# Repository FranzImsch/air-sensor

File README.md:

# Air Sensor V1.0
A small solar powered ZigBee compatible sensor with energy harvesting for temperature, humidity and VOCs.  
Features nRF52840, AEM10941, SHT40 and SGP40.

## Known Flaws
* Due to the extremely high resistor values of the voltage dividers and their corresponding errors, the set voltage limits are very inaccurate. 
* The overall performance is not completely satisfying, especially indoors pretty much no energy is harvested. (Maybe a different chip like TI's [BQ25570](https://www.ti.com/lit/ds/symlink/bq25570.pdf) could perform better.) The Sensirion sensors perform excellently.

## Software
The proper software (that uses ZigBee) is to be developed. The existing software is a very rudimentary Arduino example to test the sensors. It draws way too much power to be used.

## BOM
The interactive BOM can be found [here](https://franz.science/airsensor-v1.0-ibom/).  

## Reference
e-peas Configuration tool (for the resistors) in the resources section: [Product page](https://e-peas.com/product/aem10941/).

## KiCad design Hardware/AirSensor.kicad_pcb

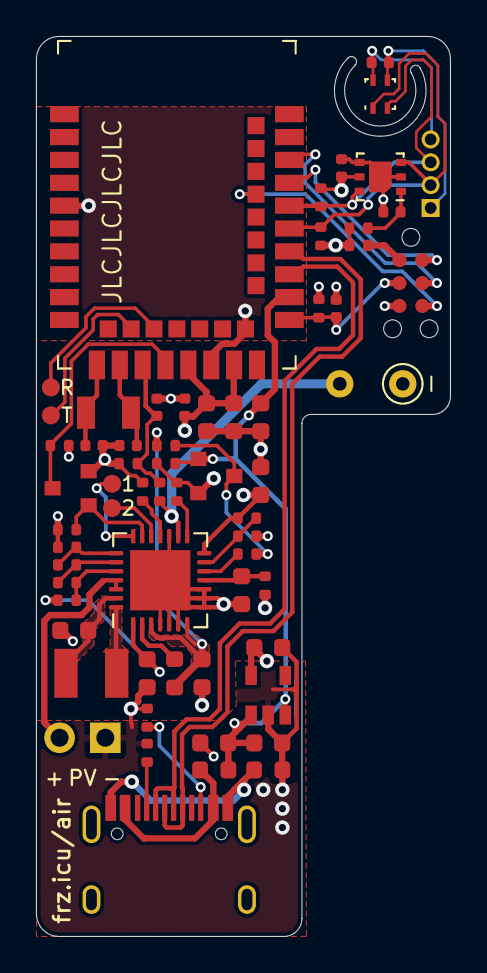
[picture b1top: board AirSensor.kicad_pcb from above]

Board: 4 copper layers, 23.0 x 50.0 mm, 63 parts (0 on the bottom side), 42 nets.

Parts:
C1, C2: 4.7µF; C_0603_1608Metric
C3: 10nF; C_0402_1005Metric
C4, C18, C24: 100nF; C_0402_1005Metric
C11: 100nF; C_0603_1608Metric
C14, C16: 2.2µF; C_0603_1608Metric
C17: 1µF; C_0603_1608Metric
C19, C20: 15pF; C_0402_1005Metric
C23, C25: 1µF; C_0402_1005Metric
C26: 22µF; C_0603_1608Metric
C27, C28, C29, C30: 10µF; C_0603_1608Metric
C31: 3.8V 30F; TPLC-3R8_30MR8X25
D1: SM141K07L; PinHeader_1x02_P2.54mm_Vertical
FB1, FB2: 120Ω; L_0603_1608Metric
J1: USB_C_Receptacle_USB2.0; USB_C_Receptacle_HRO_TYPE-C-31-M-12
J2: Tag-Connect; Tag-Connect_TC2030-IDC-NL_2x03_P1.27mm_Vertical
J3: Conn_01x04_Male; PinHeader_1x04_P1.27mm_Vertical
JP1, JP2, JP3: Jumper_NC_Small; R_0402_1005Metric
L2: 10µH; INDC3225X270N
L3: 10µH; L_0603_1608Metric
Q1, Q2: BSS138; SOT-23
R1: 10 kΩ; R_0402_1005Metric
R2, R3: 5.1kΩ; R_0402_1005Metric
R4: 0 Ω; R_0402_1005Metric
R5: 4.7Ω; R_0402_1005Metric
R6, R7: 750Ω; R_0402_1005Metric
R8: 47MΩ; R_0402_1005Metric
R9: 8.2MΩ; R_0402_1005Metric
R10: 6.04MΩ; R_0402_1005Metric
R11, R17: 22MΩ; R_0402_1005Metric
R12, R18: 16MΩ; R_0402_1005Metric
R13: 20MΩ; R_0402_1005Metric
R14: DNP; R_0402_1005Metric
R15, R16, R19: 1MΩ; R_0402_1005Metric
R20: 100kΩ; R_0402_1005Metric
SGP40_1: SGP40
SHT4x_1: SHT4x; Sensirion_SHT4x
TP1: LDOs Ready; TestPoint_Pad_D1.0mm
TP2: MPP Evaluation; TestPoint_Pad_D1.0mm
TP3, TP4: TestPoint; TestPoint_Pad_D1.0mm
U1: E73-2G4M08S1C
U2: MIC5225-1.8YM5-TR; SOT-23-5
U3: AEM10941; QFN-28-1EP_5x5mm_P0.5mm_EP3.35x3.35mm
Y2: 32.768 kHz; Crystal_SMD_3215-2Pin_3.2x1.5mm

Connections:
1.8V: C1.2, C16.1, C17.2, C18.2, C23.2, C24.2, C30.2, J3.1, R1.1, R4.2, R5.1, R6.2, R7.1, R12.1, R14.1, R16.2, SGP40_1.5, SHT4x_1.3, U1.19, U1.23, U2.5, U3.14
+VBoost: C26.2, R8.2, U3.1
+VBuck: C28.2, L3.1, R19.1, U3.3, U3.7
CapVoltage: C3.2, R17.2, R18.1, U1.15
GND: C1.1, C2.1, C3.1, C4.1, C11.2, C14.1, C16.2, C17.1, C18.1, C19.1, C20.2, C23.1, C24.1, C25.1, C26.1, C27.1, C28.1, C29.2, C30.1, C31.-, D1.1, FB1.1, J2.5, J3.4, JP1.2, JP3.2, Q1.2, Q2.2, R2.1, R3.1, R11.1, R13.2, R15.1, R18.2, R20.2, SGP40_1.2, SGP40_1.4, SGP40_1.PAD, SHT4x_1.4, U1.5, U1.21, U1.24, U2.2, U3.4, U3.5, U3.6, U3.8, U3.9, U3.10, U3.17, U3.29
I2C_SCL: J3.3, R6.1, SGP40_1.6, SHT4x_1.2, U1.35
I2C_SDA: J3.2, R7.2, SGP40_1.3, SHT4x_1.1, U1.33
unnamed: C19.2, U1.11, Y2.1
unnamed: C20.1, U1.13, Y2.2
unnamed: C25.2, R5.2, SGP40_1.1
unnamed: C27.2, L2.1, U3.27
unnamed: C29.1, R14.2, U3.11
unnamed: C31.+, R17.1, U3.16
unnamed: D1.2, U3.25, U3.26
unnamed: FB1.2, J1.A1, J1.A12, J1.B1, J1.B12
unnamed: FB2.2, J1.A4, J1.A9, J1.B4, J1.B9
unnamed: J1.A5, R2.2
unnamed: J1.B5, R3.2
unnamed: J2.1, R4.1
unnamed: JP1.1, U3.15
unnamed: JP2.1, U3.12
unnamed: JP2.2, Q2.3, R19.2
unnamed: JP3.1, U3.18
unnamed: L2.2, U3.28
unnamed: L3.2, U3.2
unnamed: Q1.1, R15.2, U3.20
unnamed: R8.1, R9.2, U3.24
unnamed: R10.1, R11.2, U3.22
unnamed: R9.1, R10.2, U3.23
unnamed: R12.2, R13.1, U3.13
unnamed: TP1.1, U3.21
unnamed: TP2.1, U3.19
RESET: C4.2, J2.3, R1.2, U1.26
RX: TP4.1, U1.16
SWDCLK: J2.4, U1.39
SWDIO: J2.2, U1.37
SWO: J2.6, U1.36
TX: TP3.1, U1.14
USB_DN: J1.A7, J1.B7, U1.29
USB_DP: J1.A6, J1.B6, U1.31
VBUS: C2.2, C11.1, C14.2, FB2.1, Q2.1, R20.1, U1.27, U2.1, U2.3
VoltageLow: Q1.3, R16.1, U1.17

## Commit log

2021-07-04 initialising repo
2021-07-04 Create CNAME
2021-07-04 ibom
2021-07-04 iBOM on GitHub Pages
2021-07-04 Readme
2021-07-15 fixed ibom and added 3d print file
2021-08-08 Adding hardware files and 1st readme revision
2021-08-08 removed deprecated CNAME
2021-10-07 added rudimentary Arduino test software
